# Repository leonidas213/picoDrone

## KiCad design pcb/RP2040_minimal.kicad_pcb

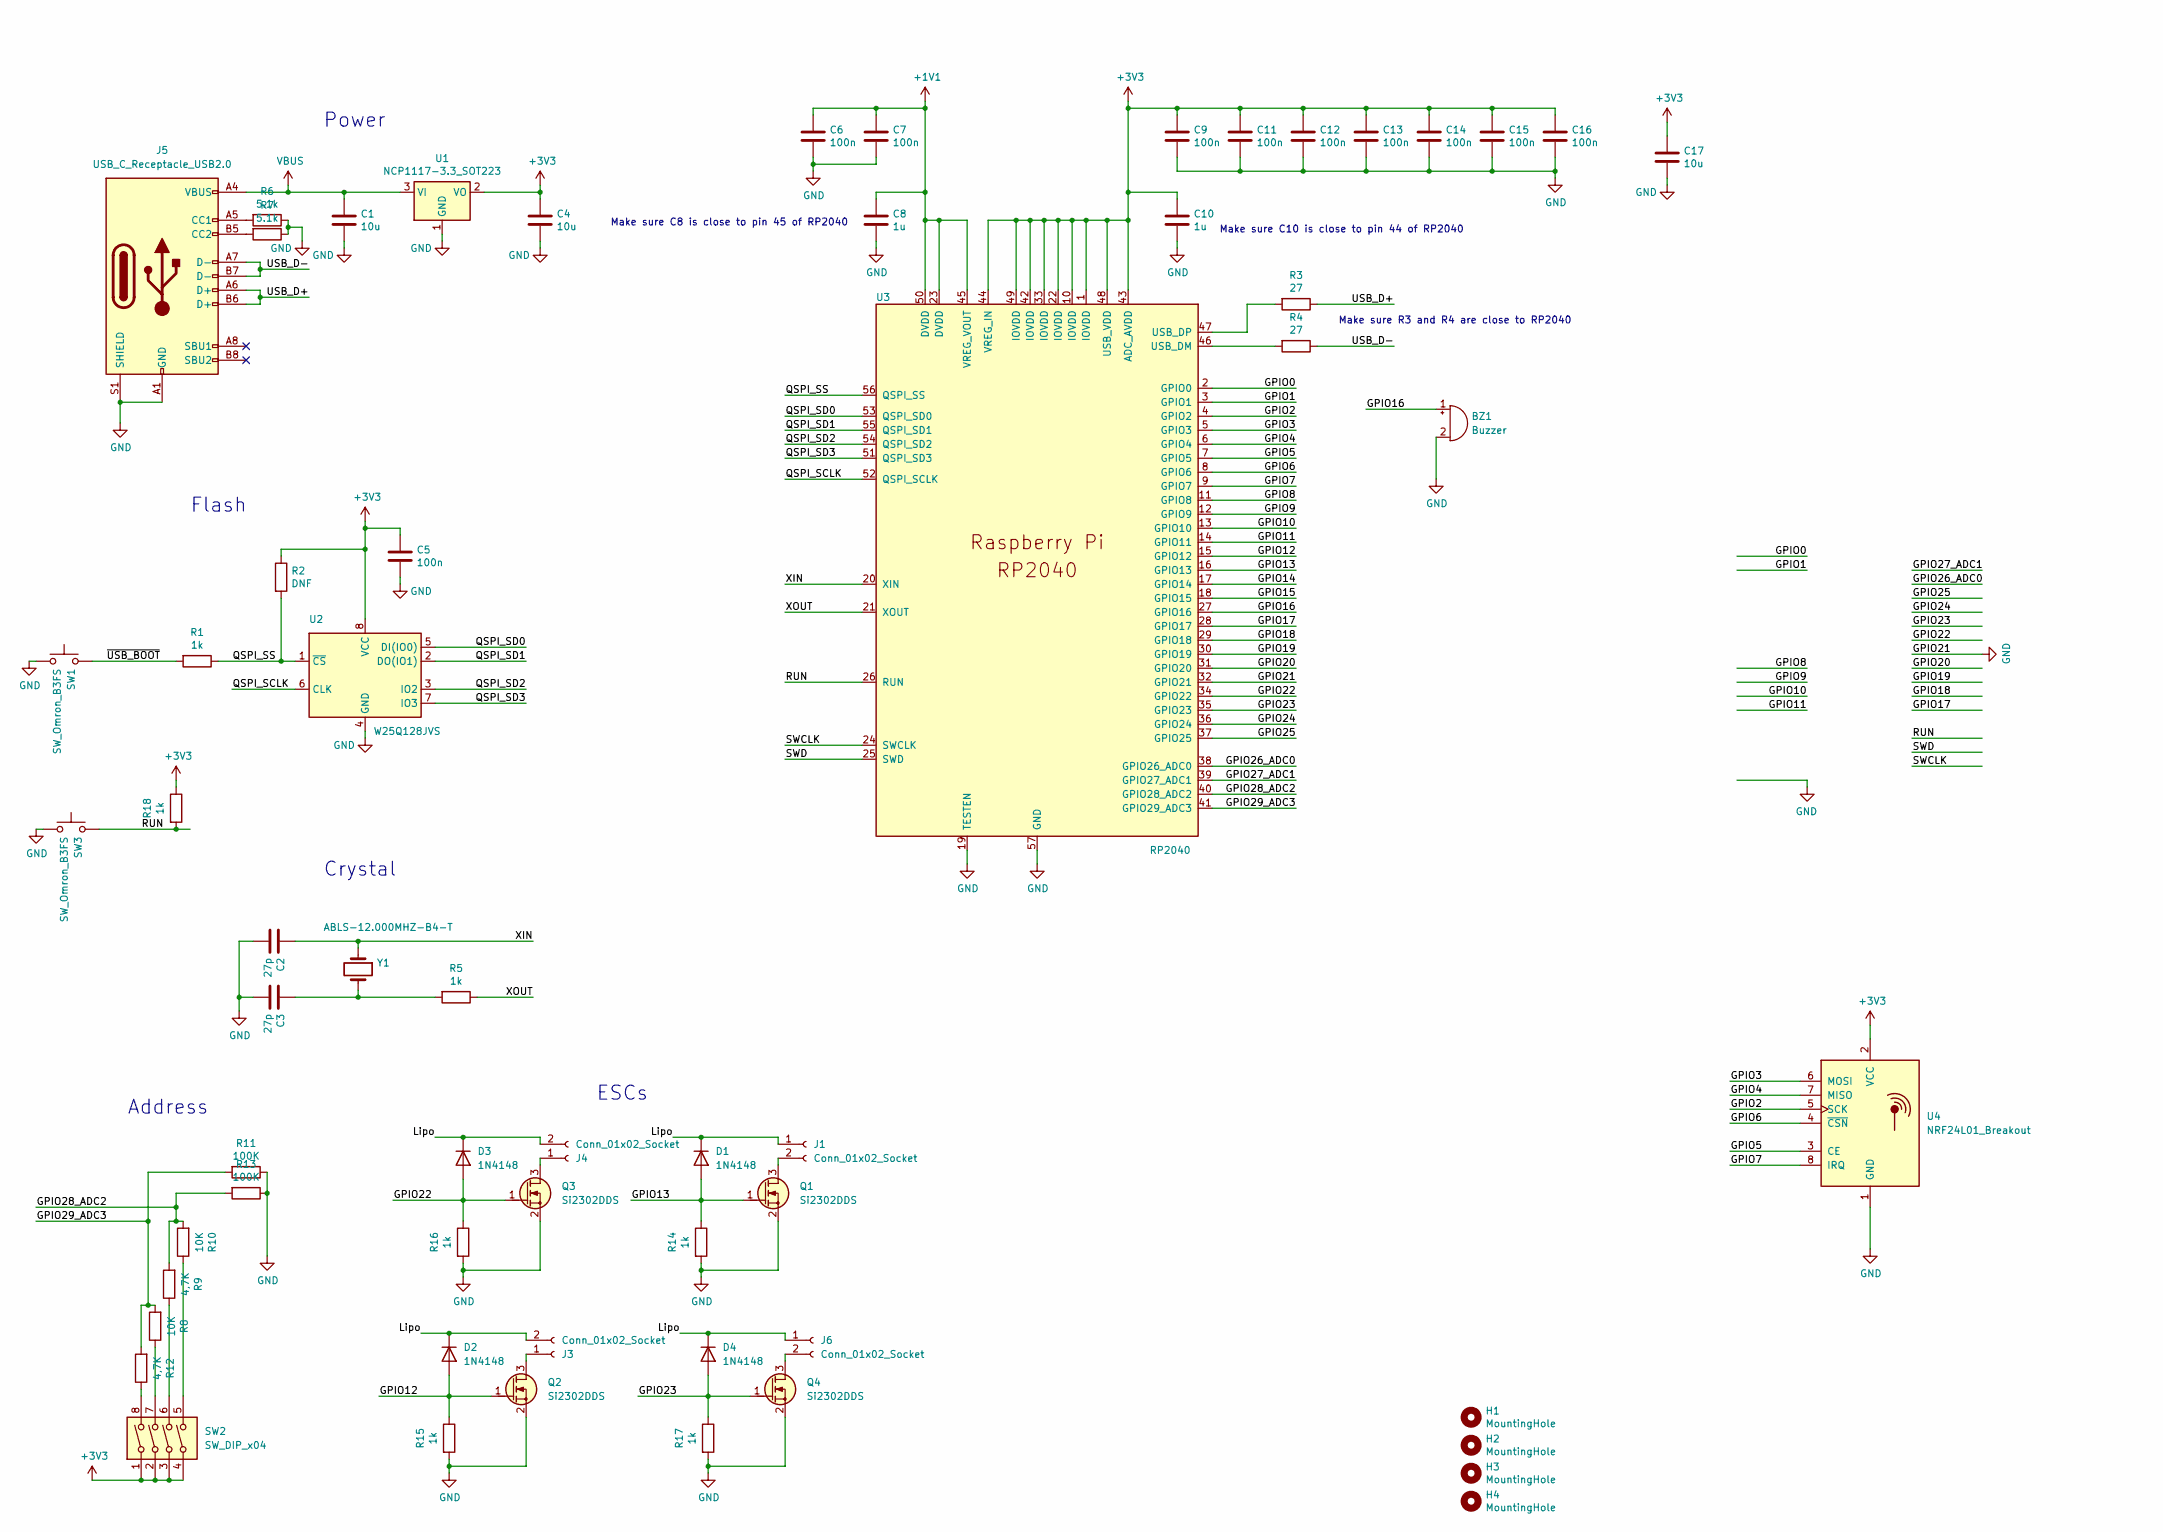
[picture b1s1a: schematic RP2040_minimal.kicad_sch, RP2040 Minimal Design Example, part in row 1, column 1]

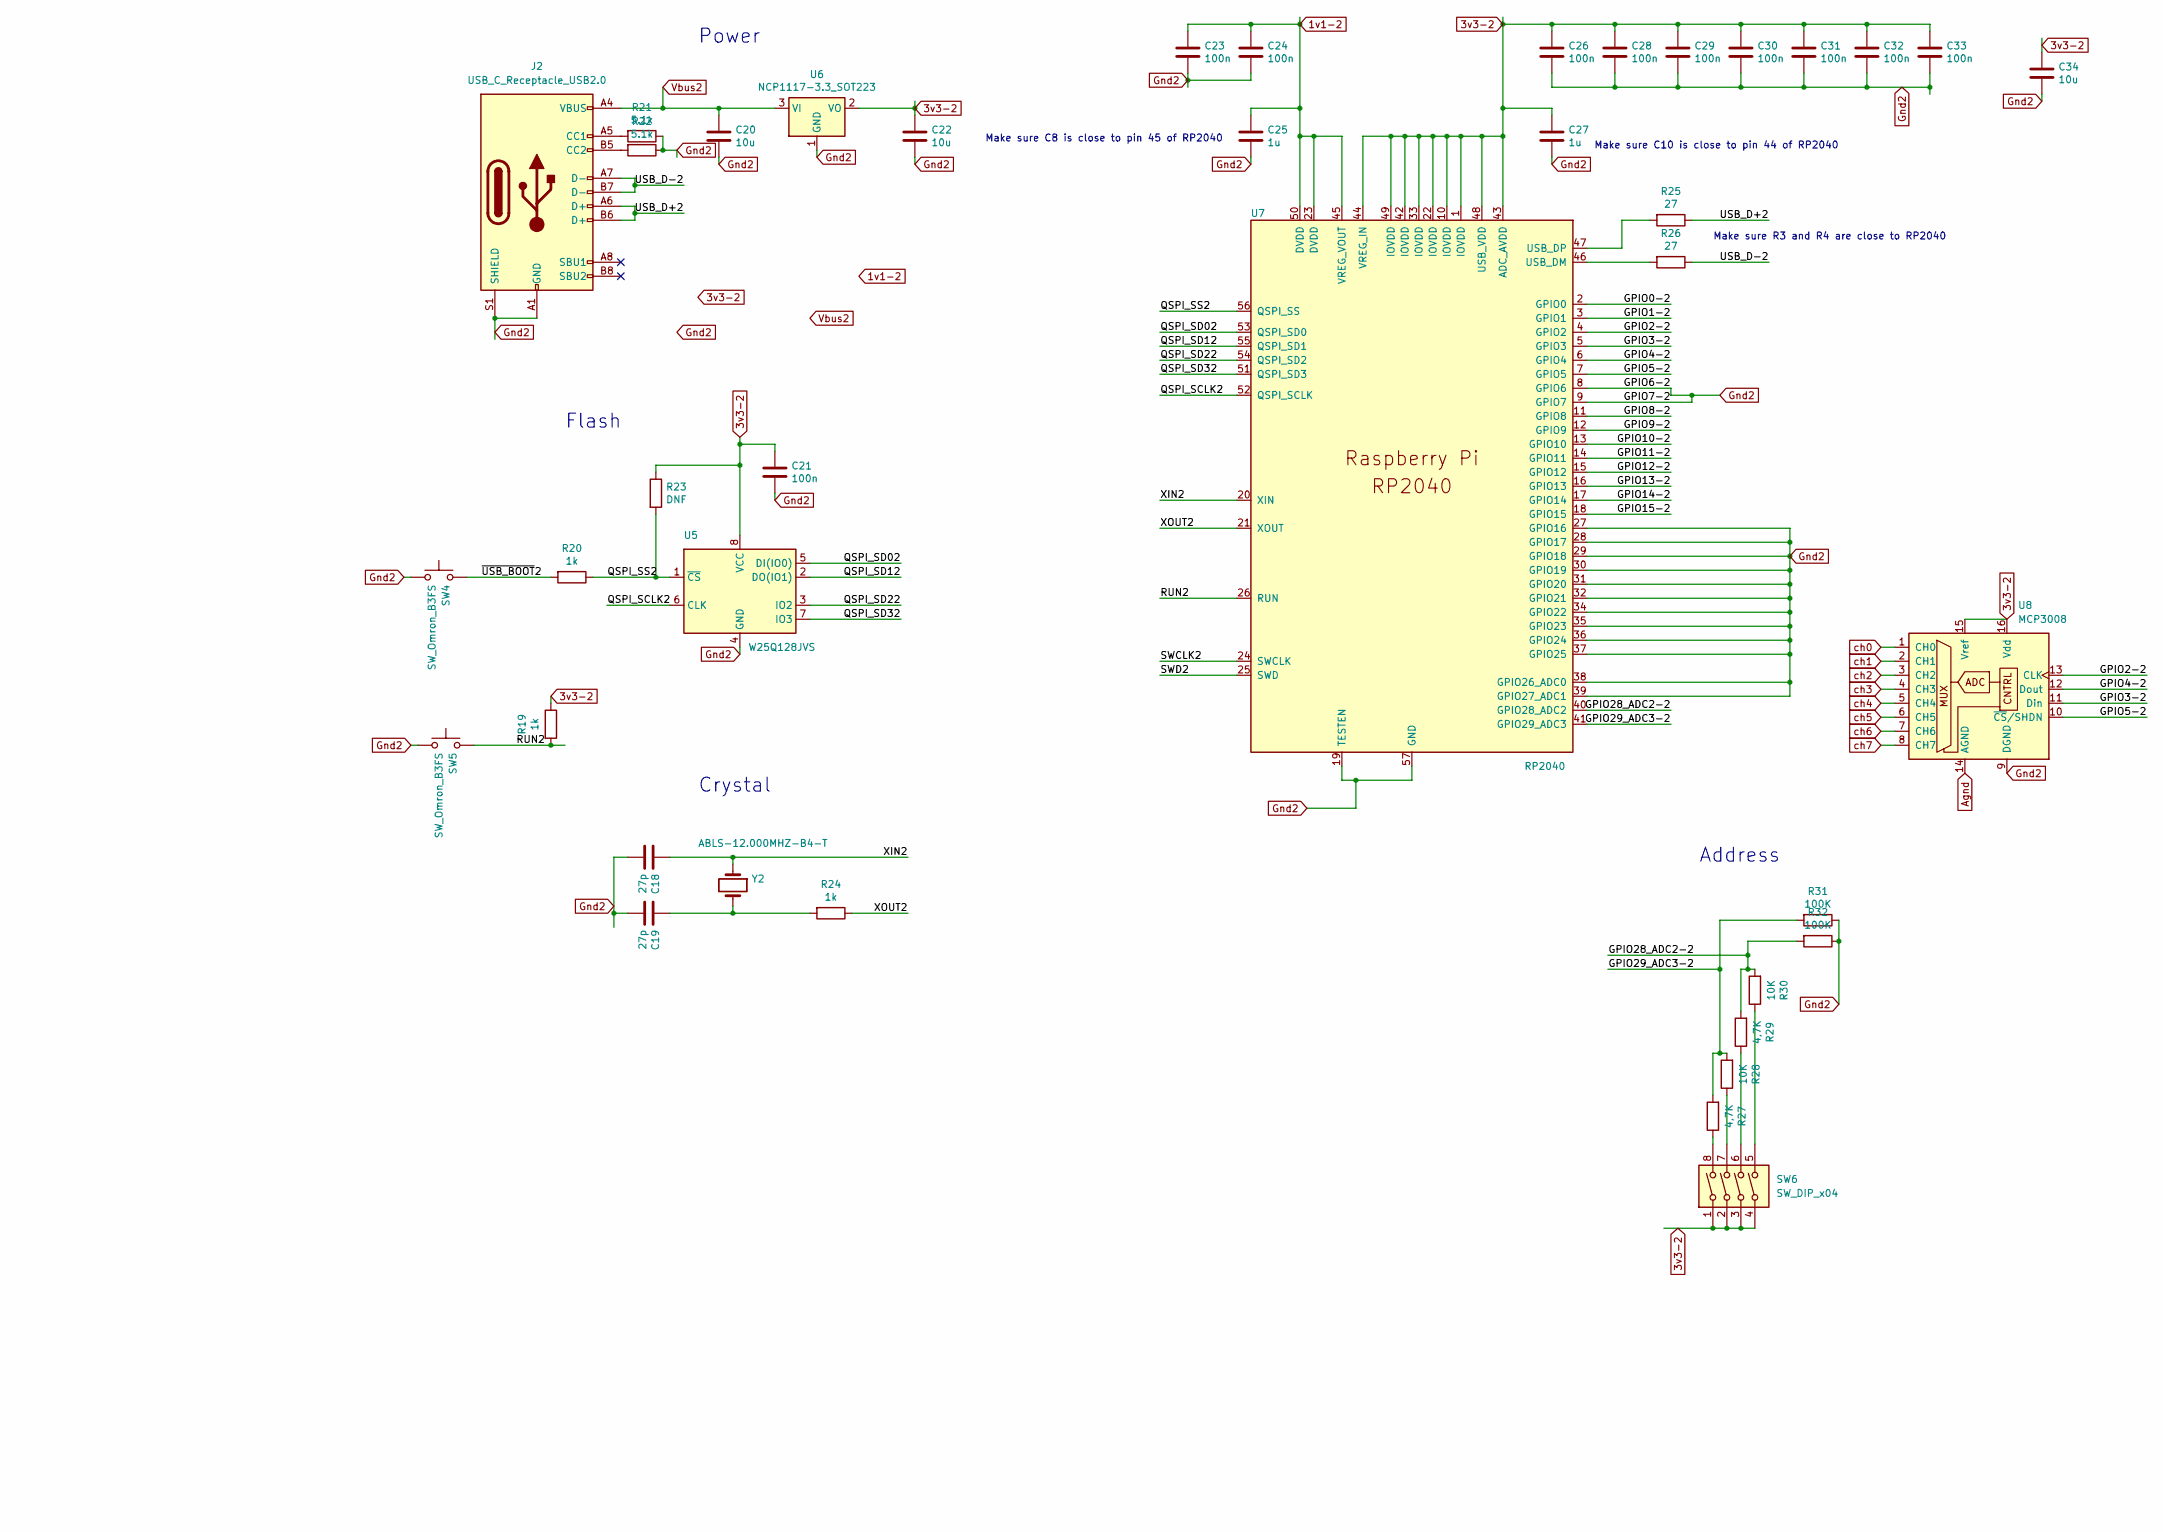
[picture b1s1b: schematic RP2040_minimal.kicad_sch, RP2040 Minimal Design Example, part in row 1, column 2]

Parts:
BZ1: Buzzer; Buzzer_12x9.5RM7.6
C1, C4, C17, C20, C22, C34: 10u; C_0805_2012Metric
C2, C3, C18, C19: 27p; C_0402_1005Metric
C5, C6, C7, C9, C11, C12, C13, C14, C15, C16, C21, C23, C24, C26, C28, C29, C30, C31, C32, C33: 100n; C_0402_1005Metric
C8, C10, C25, C27: 1u; C_0402_1005Metric
D1, D2, D3, D4: 1N4148; D_DO-35_SOD27_P7.62mm_Horizontal
H1, H2, H3, H4: MountingHole; MountingHole_2.7mm_M2.5
J1, J3, J4, J6: Conn_01x02_Socket; PinHeader_1x02_P1.27mm_Horizontal
J2, J5: USB_C_Receptacle_USB2.0; USB_C_Receptacle_GCT_USB4105-xx-A_16P_TopMnt_Horizontal
Q1, Q2, Q3, Q4: Si2302DDS; SOT-23
R1, R5, R14, R15, R16, R17, R18, R19, R20, R24: 1k; C_0402_1005Metric
R2, R23: DNF; C_0402_1005Metric
R3, R4, R25, R26: 27; C_0402_1005Metric
R6, R7, R21, R22: 5.1k; C_0402_1005Metric
R8, R10, R28, R30: 10K; C_0402_1005Metric
R9, R12, R27, R29: 4,7K; C_0402_1005Metric
R11, R13, R31, R32: 100K; C_0402_1005Metric
SW1, SW3, SW4, SW5: SW_Omron_B3FS; SW_SPST_PTS810
SW2, SW6: SW_DIP_x04; SW_DIP_SPSTx04_Slide_6.7x11.72mm_W8.61mm_P2.54mm_LowProfile
U1, U6: NCP1117-3.3_SOT223; SOT-223-3_TabPin2
U2, U5: W25Q128JVS; SOIC-8_5.23x5.23mm_P1.27mm
U3, U7: RP2040; RP2040-QFN-56
U4: NRF24L01_Breakout; nRF24L01_Breakout
U8: MCP3008; DIP-16_W7.62mm_Socket
Y1, Y2: ABLS-12.000MHZ-B4-T; Crystal_SMD_5032-2Pin_5.0x3.2mm_HandSoldering

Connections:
1v1-2: C23.1, C24.1, C25.1, U7.23 (DVDD), U7.45 (VREG_VOUT), U7.50 (DVDD)
3v3-2: C21.1, C22.1, C26.1, C27.1, C28.1, C29.1, C30.1, C31.1, C32.1, C33.1, C34.1, R19.1, R23.1, SW6.1, SW6.2, SW6.3, SW6.4, U5.8 (VCC), U6.2 (VO), U7.1 (IOVDD), U7.10 (IOVDD), U7.22 (IOVDD), U7.33 (IOVDD), U7.42 (IOVDD), U7.43 (ADC_AVDD), U7.44 (VREG_IN), U7.48 (USB_VDD), U7.49 (IOVDD), U8.15 (Vref), U8.16 (Vdd)
+1V1: C6.1, C7.1, C8.1, U3.23 (DVDD), U3.45 (VREG_VOUT), U3.50 (DVDD)
+3V3: C4.1, C5.1, C9.1, C10.1, C11.1, C12.1, C13.1, C14.1, C15.1, C16.1, C17.1, R2.1, R18.1, SW2.1, SW2.2, SW2.3, SW2.4, U1.2 (VO), U2.8 (VCC), U3.1 (IOVDD), U3.10 (IOVDD), U3.22 (IOVDD), U3.33 (IOVDD), U3.42 (IOVDD), U3.43 (ADC_AVDD), U3.44 (VREG_IN), U3.48 (USB_VDD), U3.49 (IOVDD), U4.2 (VCC)
/GPIO0: U3.2 (GPIO0)
/GPIO0-2: U7.2 (GPIO0)
/GPIO1: U3.3 (GPIO1)
/GPIO1-2: U7.3 (GPIO1)
/GPIO2: U3.4 (GPIO2), U4.5 (SCK)
/GPIO2-2: U7.4 (GPIO2), U8.13 (CLK)
/GPIO3: U3.5 (GPIO3), U4.6 (MOSI)
/GPIO3-2: U7.5 (GPIO3), U8.11 (Din)
/GPIO4: U3.6 (GPIO4), U4.7 (MISO)
/GPIO4-2: U7.6 (GPIO4), U8.12 (Dout)
/GPIO5: U3.7 (GPIO5), U4.3 (CE)
/GPIO5-2: U7.7 (GPIO5), U8.10 (~CS/SHDN)
/GPIO6: U3.8 (GPIO6), U4.4 (~CSN)
/GPIO7: U3.9 (GPIO7), U4.8 (IRQ)
/GPIO8: U3.11 (GPIO8)
/GPIO8-2: U7.11 (GPIO8)
/GPIO9: U3.12 (GPIO9)
/GPIO9-2: U7.12 (GPIO9)
/GPIO10: U3.13 (GPIO10)
/GPIO10-2: U7.13 (GPIO10)
/GPIO11: U3.14 (GPIO11)
/GPIO11-2: U7.14 (GPIO11)
/GPIO12: D2.2 (A), Q2.1 (G), R15.1, U3.15 (GPIO12)
/GPIO12-2: U7.15 (GPIO12)
/GPIO13: D1.2 (A), Q1.1 (G), R14.1, U3.16 (GPIO13)
/GPIO13-2: U7.16 (GPIO13)
/GPIO14: U3.17 (GPIO14)
/GPIO14-2: U7.17 (GPIO14)
/GPIO15: U3.18 (GPIO15)
/GPIO15-2: U7.18 (GPIO15)
/GPIO16: BZ1.1 (-), U3.27 (GPIO16)
/GPIO17: U3.28 (GPIO17)
/GPIO18: U3.29 (GPIO18)
/GPIO19: U3.30 (GPIO19)
/GPIO20: U3.31 (GPIO20)
/GPIO22: D3.2 (A), Q3.1 (G), R16.1, U3.34 (GPIO22)
/GPIO23: D4.2 (A), Q4.1 (G), R17.1, U3.35 (GPIO23)
/GPIO24: U3.36 (GPIO24)
/GPIO25: U3.37 (GPIO25)
/GPIO26_ADC0: U3.38 (GPIO26_ADC0)
/GPIO27_ADC1: U3.39 (GPIO27_ADC1)
/GPIO28_ADC2: R9.2, R10.2, R13.2, U3.40 (GPIO28_ADC2)
/GPIO28_ADC2-2: R29.2, R30.2, R32.2, U7.40 (GPIO28_ADC2)
/GPIO29_ADC3: R8.2, R11.2, R12.2, U3.41 (GPIO29_ADC3)
/GPIO29_ADC3-2: R27.2, R28.2, R31.2, U7.41 (GPIO29_ADC3)
/Lipo: D1.1 (K), D2.1 (K), D3.1 (K), D4.1 (K), J1.1, J3.2, J4.2, J6.1
/QSPI_SCLK: U2.6 (CLK), U3.52 (QSPI_SCLK)
/QSPI_SCLK2: U5.6 (CLK), U7.52 (QSPI_SCLK)
/QSPI_SD0: U2.5 (DI(IO0)), U3.53 (QSPI_SD0)
/QSPI_SD1: U2.2 (DO(IO1)), U3.55 (QSPI_SD1)
/QSPI_SD2: U2.3 (IO2), U3.54 (QSPI_SD2)
/QSPI_SD02: U5.5 (DI(IO0)), U7.53 (QSPI_SD0)
/QSPI_SD3: U2.7 (IO3), U3.51 (QSPI_SD3)
/QSPI_SD12: U5.2 (DO(IO1)), U7.55 (QSPI_SD1)
/QSPI_SD22: U5.3 (IO2), U7.54 (QSPI_SD2)
/QSPI_SD32: U5.7 (IO3), U7.51 (QSPI_SD3)
/QSPI_SS: R1.1, R2.2, U2.1 (~CS), U3.56 (QSPI_SS)
/QSPI_SS2: R20.1, R23.2, U5.1 (~CS), U7.56 (QSPI_SS)
/RUN: R18.2, SW3.2, U3.26 (RUN)
/RUN2: R19.2, SW5.2, U7.26 (RUN)
/SWCLK: U3.24 (SWCLK)
/SWCLK2: U7.24 (SWCLK)
/SWD: U3.25 (SWD)
/SWD2: U7.25 (SWD)
/USB_D+: J5.A6 (D+), J5.B6 (D+), R3.1
/USB_D+2: J2.A6 (D+), J2.B6 (D+), R25.1
/USB_D-: J5.A7 (D-), J5.B7 (D-), R4.1
/USB_D-2: J2.A7 (D-), J2.B7 (D-), R26.1
/XIN: C2.1, U3.20 (XIN), Y1.1
/XIN2: C18.1, U7.20 (XIN), Y2.1
/XOUT: R5.1, U3.21 (XOUT)
/XOUT2: R24.1, U7.21 (XOUT)
/~USB_BOOT: R1.2, SW1.2
/~USB_BOOT2: R20.2, SW4.2
Agnd: U8.14 (AGND)
GND: BZ1.2 (+), C1.2, C2.2, C3.2, C4.2, C5.2, C6.2, C7.2, C8.2, C9.2, C10.2, C11.2, C12.2, C13.2, C14.2, C15.2, C16.2, C17.2, J5.A1 (GND), J5.A12 (GND), J5.B1 (GND), J5.B12 (GND), J5.S1 (SHIELD), Q1.2 (S), Q2.2 (S), Q3.2 (S), Q4.2 (S), R6.1, R7.1, R11.1, R13.1, R14.2, R15.2, R16.2, R17.2, SW1.1, SW3.1, U1.1 (GND), U2.4 (GND), U3.19 (TESTEN), U3.32 (GPIO21), U3.57 (GND), U4.1 (GND)
Gnd2: C18.2, C19.2, C20.2, C21.2, C22.2, C23.2, C24.2, C25.2, C26.2, C27.2, C28.2, C29.2, C30.2, C31.2, C32.2, C33.2, C34.2, J2.A1 (GND), J2.A12 (GND), J2.B1 (GND), J2.B12 (GND), J2.S1 (SHIELD), R21.1, R22.1, R31.1, R32.1, SW4.1, SW5.1, U5.4 (GND), U6.1 (GND), U7.8 (GPIO6), U7.9 (GPIO7), U7.19 (TESTEN), U7.27 (GPIO16), U7.28 (GPIO17), U7.29 (GPIO18), U7.30 (GPIO19), U7.31 (GPIO20), U7.32 (GPIO21), U7.34 (GPIO22), U7.35 (GPIO23), U7.36 (GPIO24), U7.37 (GPIO25), U7.38 (GPIO26_ADC0), U7.39 (GPIO27_ADC1), U7.57 (GND), U8.9 (DGND)
unnamed: C3.1, R5.2, Y1.2
unnamed: C19.1, R24.2, Y2.2
unnamed: J1.2, Q1.3 (D)
unnamed: J2.A5 (CC1), R21.2
unnamed: J2.B5 (CC2), R22.2
unnamed: J3.1, Q2.3 (D)
unnamed: J4.1, Q3.3 (D)
unnamed: J5.A5 (CC1), R6.2
unnamed: J5.B5 (CC2), R7.2
unnamed: J6.2, Q4.3 (D)
unnamed: R8.1, SW2.7
unnamed: R9.1, SW2.6
unnamed: R10.1, SW2.5
unnamed: R12.1, SW2.8
unnamed: R27.1, SW6.8
unnamed: R28.1, SW6.7
unnamed: R29.1, SW6.6
unnamed: R30.1, SW6.5
unnamed: R4.2, U3.46 (USB_DM)
unnamed: R3.2, U3.47 (USB_DP)
unnamed: R26.2, U7.46 (USB_DM)
unnamed: R25.2, U7.47 (USB_DP)
VBUS: C1.1, J5.A4 (VBUS), J5.A9 (VBUS), J5.B4 (VBUS), J5.B9 (VBUS), U1.3 (VI)
Vbus2: C20.1, J2.A4 (VBUS), J2.A9 (VBUS), J2.B4 (VBUS), J2.B9 (VBUS), U6.3 (VI)
ch0: U8.1 (CH0)
ch1: U8.2 (CH1)
ch2: U8.3 (CH2)
ch3: U8.4 (CH3)
ch4: U8.5 (CH4)
ch5: U8.6 (CH5)
ch6: U8.7 (CH6)
ch7: U8.8 (CH7)

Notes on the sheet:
Flash
Power
Crystal
Make sure C10 is close to pin 44 of RP2040
Address
Make sure R3 and R4 are close to RP2040
Make sure C8 is close to pin 45 of RP2040
ESCs

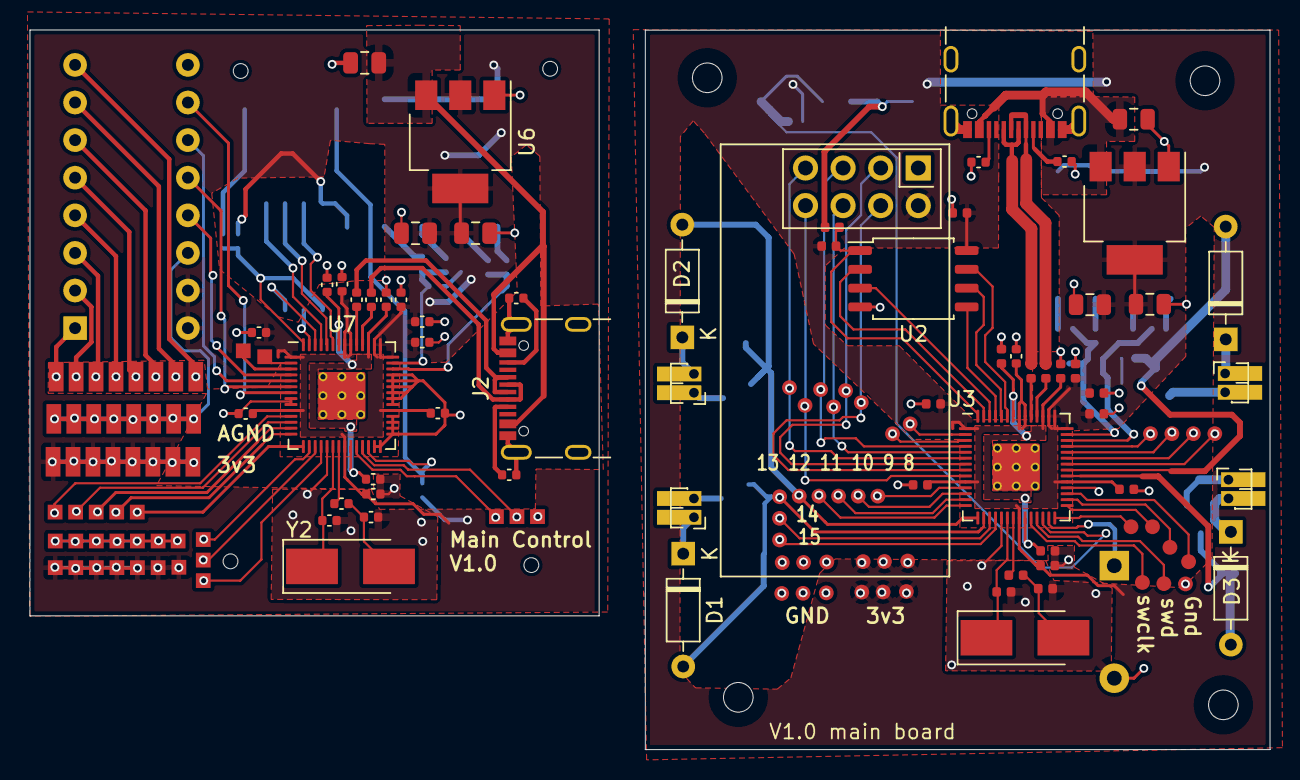
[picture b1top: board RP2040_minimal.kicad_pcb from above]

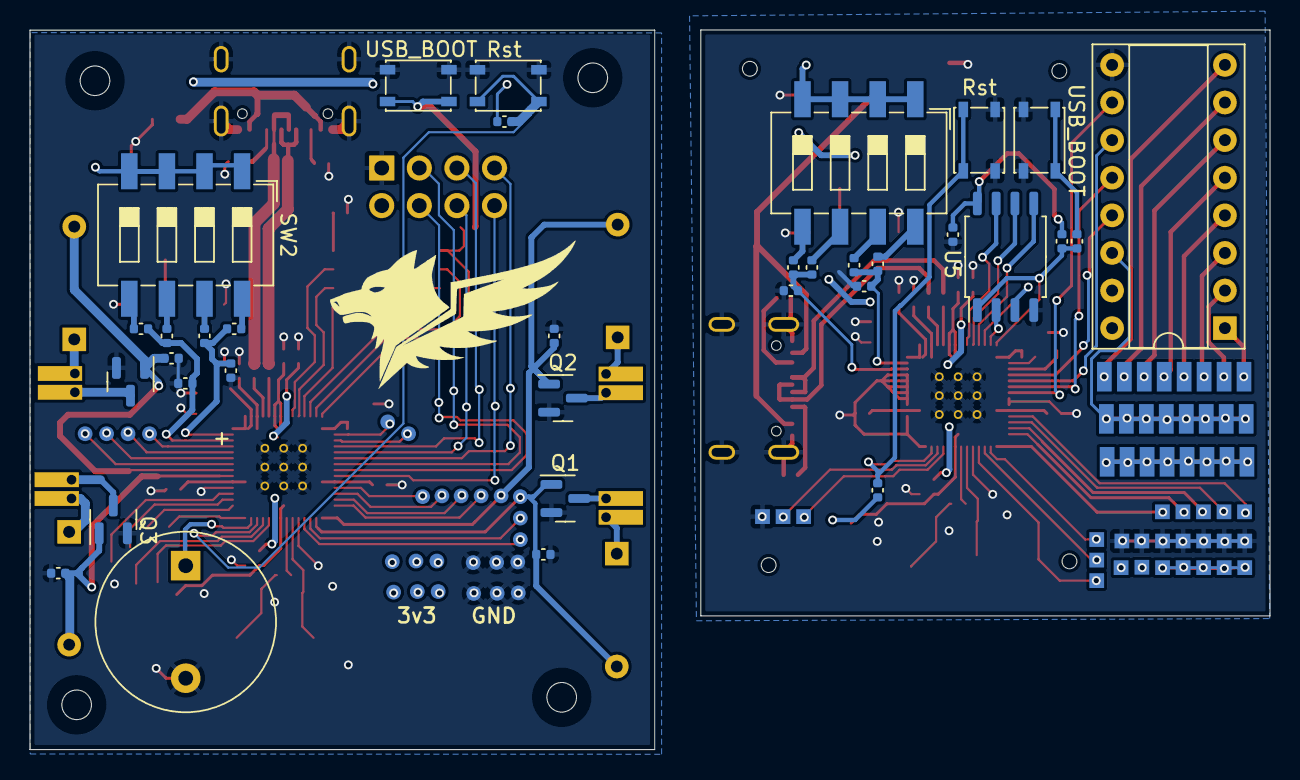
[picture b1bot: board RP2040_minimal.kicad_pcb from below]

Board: 2 copper layers, 83.8 x 48.6 mm, 105 parts (34 on the bottom side), 74 nets.

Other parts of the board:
H1#2, H2#2, H3#2, H4#2: MountingHole; MountingHole_2.7mm_M2.5
